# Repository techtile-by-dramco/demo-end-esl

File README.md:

# Energy Neutral Device Demo

In this repository, KU Leuven presents a portable, energy-neutral device demonstrator. The demonstrator showcases the potential of ambient energy harvesting, with a particular emphasis on RF energy harvesting. Its primary objective is to demonstrate the feasibility of a realistic use case, illustrating how low-power devices can operate without conventional power sources. This demonstrator includes an RF-powered Electronic Shelf Label (ESL) that operates entirely without batteries. Instead, the system relies on an aluminium electrolytic capacitor as a short-term energy storage element.

<td></td>

## ToDo
- Add PLL board as RF source

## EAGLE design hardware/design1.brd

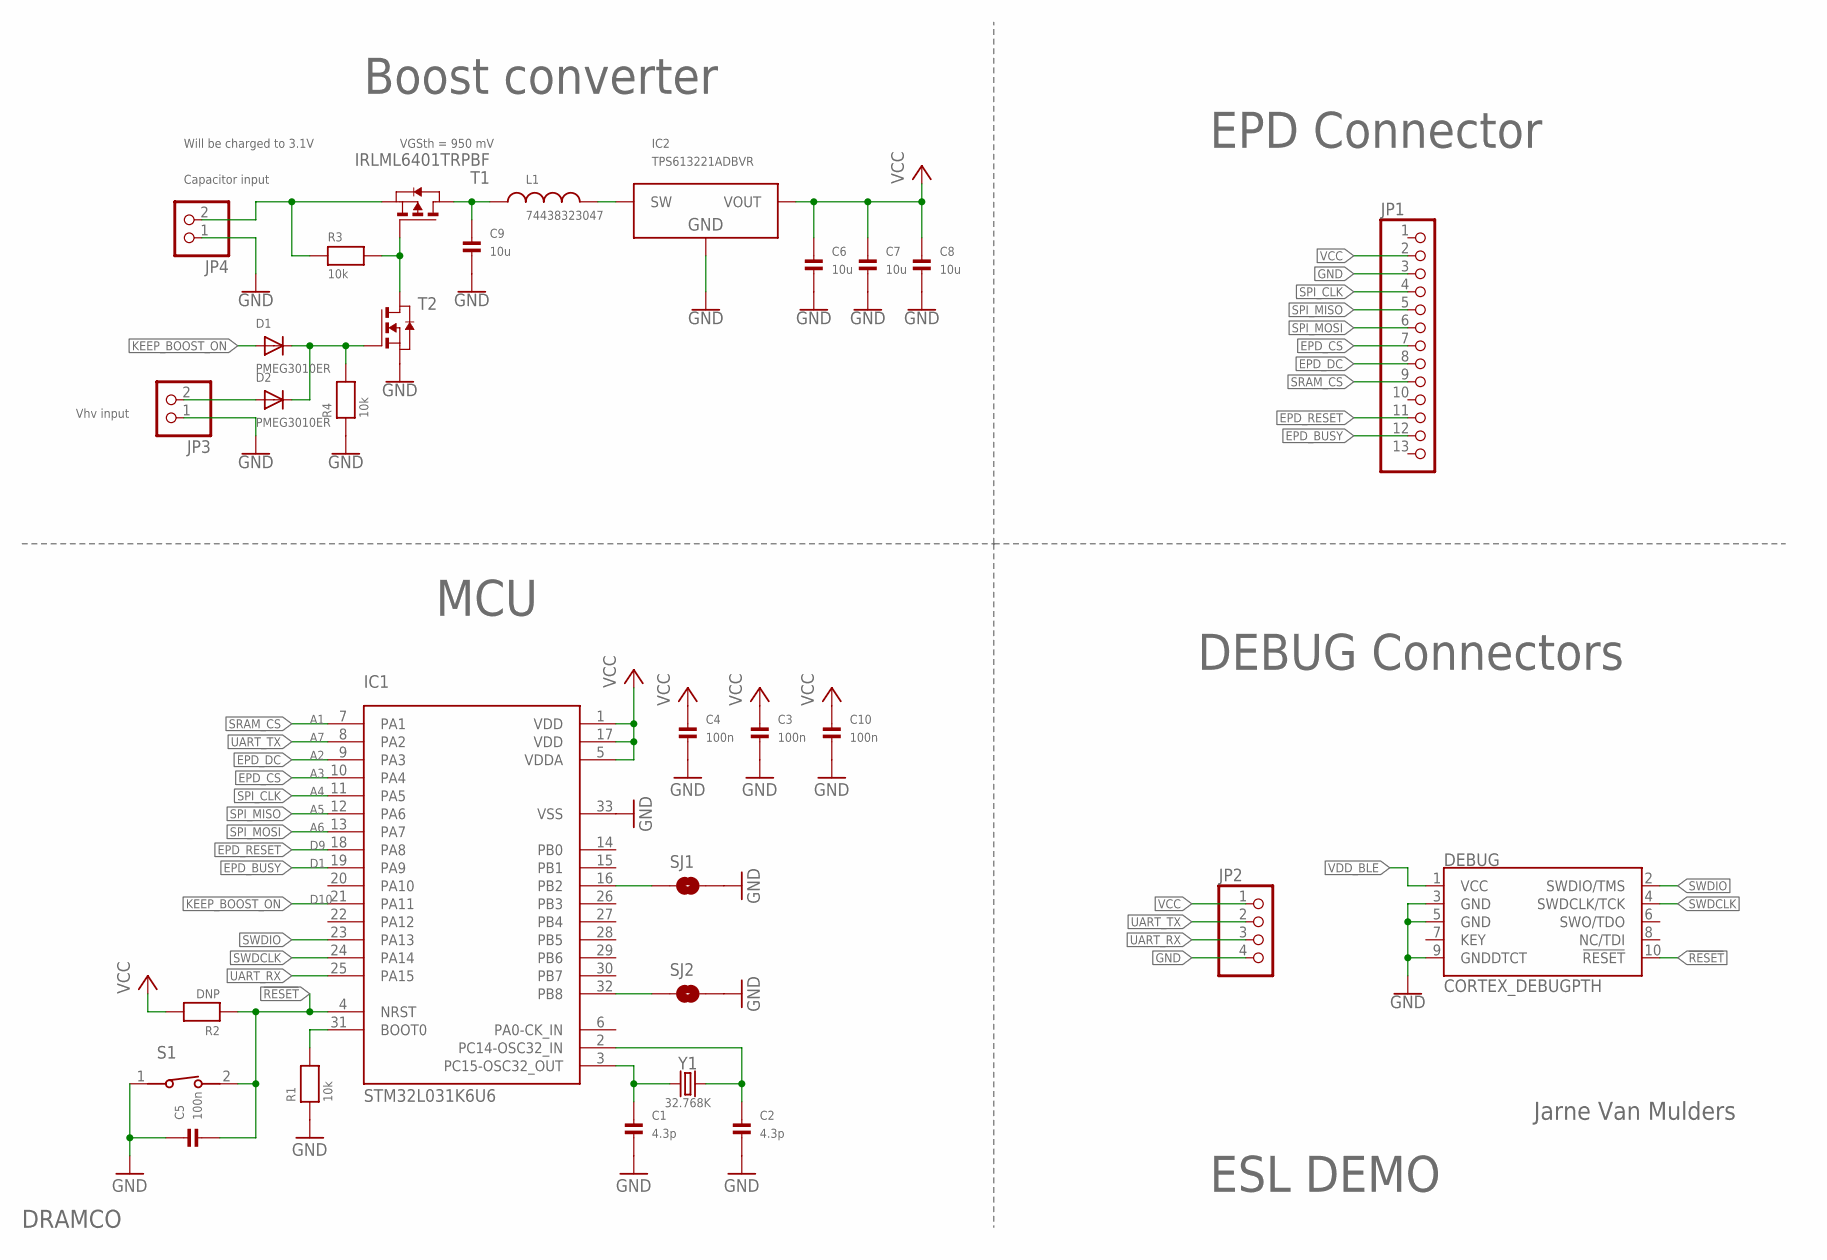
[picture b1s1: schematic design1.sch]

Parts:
C1, C2: 4.3p; 0603
C3, C4, C5, C10: 100n; 0603
C6, C7, C8, C9: 10u; 0805
D1, D2: PMEG3010ER; SOD-323
DEBUG: CORTEX_DEBUGPTH; 2X5-PTH-1.27MM
IC1: STM32L031K6U6; UFQFPN32
IC2: TPS61322XX; SOT95P280X145-5N
JP1: HEADER-1X13; 1X13_ROUND_70
JP2: HEADER-1X4ROUND; 1X04_ROUND
JP3, JP4: HEADER-1X2ROUND; 1X02_ROUND
L1: 74438323047; WE-MAIA_2510
R1, R3, R4: 10k; 0603
R2: DNP; 0603
S1: 434111043826
SJ1, SJ2: SOLDERJUMPERNO; SJ_2S-NO
T1: IRLML6401TRPBF; SOT-23
T2: NMOSSOT23; SOT-23
Y1: 32.768K; CRYSTAL-SMD-3.2X1.5MM

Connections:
!RESET!: C5.2, DEBUG.10 (!RESET), IC1.4 (NRST), R2.1, S1.2
EPD_BUSY: IC1.19 (PA9), JP1.12
EPD_CS: IC1.10 (PA4), JP1.7
EPD_DC: IC1.9 (PA3), JP1.8
EPD_RESET: IC1.18 (PA8), JP1.11
GND: C1.2, C2.2, C3.2, C4.2, C5.1, C6.2, C7.2, C8.2, C9.2, C10.2, DEBUG.3 (GND), DEBUG.5 (GND), DEBUG.9 (GNDDTCT), IC1.33 (VSS), IC2.2 (GND), JP1.3, JP2.4, JP3.1, JP4.1, R1.1, R4.1, S1.1, SJ1.2, SJ2.2, T2.2 (S)
KEEP_BOOST_ON: D1.A, IC1.21 (PA11)
unnamed: IC1.31 (BOOT0), R1.2
unnamed: C2.1, IC1.2 (PC14-OSC32_IN), Y1.P$2 (2)
unnamed: C1.1, IC1.3 (PC15-OSC32_OUT), Y1.P$1 (1)
unnamed: IC1.16 (PB2), SJ1.1
unnamed: IC1.32 (PB8), SJ2.1
unnamed: C9.1, L1.1, T1.1 (D)
unnamed: IC2.1 (SW), L1.2
unnamed: D1.C, D2.C, R4.2, T2.3 (G)
unnamed: R3.2, T1.3 (G), T2.1 (D)
unnamed: JP4.2, R3.1, T1.2 (S)
unnamed: D2.A, JP3.2
SPI_CLK: IC1.11 (PA5), JP1.4
SPI_MISO: IC1.12 (PA6), JP1.5
SPI_MOSI: IC1.13 (PA7), JP1.6
SRAM_CS: IC1.7 (PA1), JP1.9
SWDCLK: DEBUG.4 (SWDCLK/TCK), IC1.24 (PA14)
SWDIO: DEBUG.2 (SWDIO/TMS), IC1.23 (PA13)
UART_RX: IC1.25 (PA15), JP2.3
UART_TX: IC1.8 (PA2), JP2.2
VCC: C3.1, C4.1, C6.1, C7.1, C8.1, C10.1, IC1.1 (VDD), IC1.5 (VDDA), IC1.17 (VDD), IC2.4 (VOUT), JP1.2, JP2.1, R2.2
VDD_BLE: DEBUG.1 (VCC)

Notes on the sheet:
D10
Vhv input
Capacitor input
Will be charged to 3.1V
VGSth = 950 mV
TPS613221ADBVR
Boost converter
MCU
DEBUG Connectors
EPD Connector
Jarne Van Mulders
DRAMCO
ESL DEMO

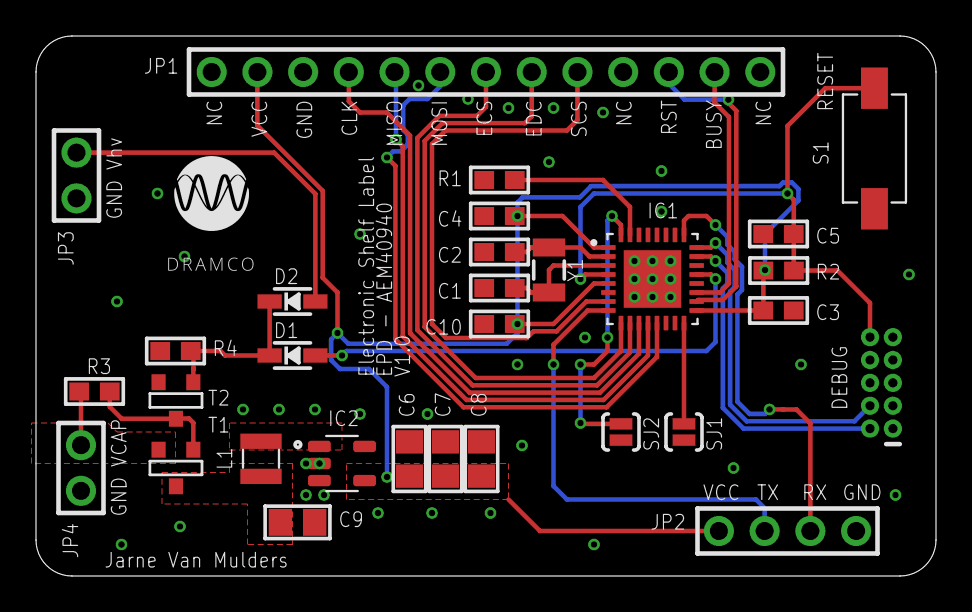
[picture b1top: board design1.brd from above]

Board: 2 copper layers, 50.0 x 30.0 mm, 30 parts (0 on the bottom side), 27 nets.

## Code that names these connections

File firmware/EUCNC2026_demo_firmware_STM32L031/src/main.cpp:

#include <Arduino.h>
#include "Adafruit_ThinkInk.h"
#include <EEPROM.h>

#define EPD_DC        A2//10
#define EPD_CS        A3//9
#define EPD_BUSY      D1//7 // can set to -1 to not use a pin (will wait a fixed delay)
#define SRAM_CS       A1//6
#define EPD_RESET     D9//8  // can set to -1 and share with microcontroller Reset!
#define EPD_SPI       &SPI // primary SPI

#define SPI1_SCK      A4
#define SPI1_MISO     A5
#define SPI1_MOSI     A6

#define KEEP_BOOST_ON D10

//  Frame number (saved in EEPROM)
uint8_t frame_number;
int eeAddress = 0;   // Location we want the data to be put.

//  Static void functions
static void setup_esl(String price);

//  EPD object
ThinkInk_213_Mono_BN display(EPD_DC, EPD_RESET, EPD_CS, SRAM_CS, EPD_BUSY, EPD_SPI);


//  Configure SYSTEM clock - NXP
extern "C" void SystemClock_Config(void){
 RCC_OscInitTypeDef RCC_OscInitStruct = {0};
  RCC_ClkInitTypeDef RCC_ClkInitStruct = {0};
  RCC_PeriphCLKInitTypeDef PeriphClkInit = {0};

  /** Configure the main internal regulator output voltage
  */
  __HAL_PWR_VOLTAGESCALING_CONFIG(PWR_REGULATOR_VOLTAGE_SCALE1);

  /** Initializes the RCC Oscillators according to the specified parameters
  * in the RCC_OscInitTypeDef structure.
  */
  RCC_OscInitStruct.OscillatorType = RCC_OSCILLATORTYPE_LSI|RCC_OSCILLATORTYPE_MSI;
  RCC_OscInitStruct.LSIState = RCC_LSI_ON;
  RCC_OscInitStruct.MSIState = RCC_MSI_ON;
  RCC_OscInitStruct.MSICalibrationValue = 0;
  RCC_OscInitStruct.MSIClockRange = RCC_MSIRANGE_6;
  RCC_OscInitStruct.PLL.PLLState = RCC_PLL_NONE;
  if (HAL_RCC_OscConfig(&RCC_OscInitStruct) != HAL_OK)
  {
    Error_Handler();
  }

  /** Initializes the CPU, AHB and APB buses clocks
  */
  RCC_ClkInitStruct.ClockType = RCC_CLOCKTYPE_HCLK|RCC_CLOCKTYPE_SYSCLK
                              |RCC_CLOCKTYPE_PCLK1|RCC_CLOCKTYPE_PCLK2;
  RCC_ClkInitStruct.SYSCLKSource = RCC_SYSCLKSOURCE_MSI;
  RCC_ClkInitStruct.AHBCLKDivider = RCC_SYSCLK_DIV1;
  RCC_ClkInitStruct.APB1CLKDivider = RCC_HCLK_DIV1;
  RCC_ClkInitStruct.APB2CLKDivider = RCC_HCLK_DIV1;

  if (HAL_RCC_ClockConfig(&RCC_ClkInitStruct, FLASH_LATENCY_0) != HAL_OK)
  {
    Error_Handler();
  }
  PeriphClkInit.PeriphClockSelection = RCC_PERIPHCLK_RTC;
  PeriphClkInit.RTCClockSelection = RCC_RTCCLKSOURCE_LSI;
  if (HAL_RCCEx_PeriphCLKConfig(&PeriphClkInit) != HAL_OK)
  {
    Error_Handler();
  }
}


void setup() {

  Serial.begin(115200);
  while (!Serial) {
    delay(10);
  }

  pinMode(LED_BUILTIN, OUTPUT);   //  Set buildin LED as output
  pinMode(EPD_CS, OUTPUT);        //  Set SS as output

  // SPI config
  SPI.setMOSI(SPI1_MOSI);
  SPI.setMISO(SPI1_MISO);
  SPI.setSCLK(SPI1_SCK);

  //  OVERRULE - Keep BOOST converter ON
  pinMode(KEEP_BOOST_ON, OUTPUT);
  digitalWrite(KEEP_BOOST_ON, HIGH);

  Serial.println("Adafruit EPD full update test in mono");
  display.begin(THINKINK_MONO);
}

void loop() {

  Serial.println("hello");
  
  //  Keep boost on for 3V3 supply voltage during EPD update
  digitalWrite(KEEP_BOOST_ON, HIGH);

  //  Get frame number for EEPROM
  uint8_t new_frame_number;
  frame_number = EEPROM.read(eeAddress);

  //  Decide with update will be performed
  switch (frame_number){
    // ESL layout with price 0.75 dollar
    case 0:
      setup_esl("$0.75");
      new_frame_number = 1;
      break;
    
    // ESL layout with price 1.4 dollar
    case 1:
      setup_esl("$1.40");
      new_frame_number = 2;
      break;
    
    // ESL layout with price 2.5 dollar
    case 2:
      setup_esl("$2.50");
      new_frame_number = 3;
      break;
    
    // Default
    default:
      break;
  }

  //  Store case number in EEPROM
  EEPROM.put(eeAddress, new_frame_number);

  //  Disable 3V3 --> DEADLOCK
  digitalWrite(KEEP_BOOST_ON, LOW);
  delay(500);
}


void setup_esl(String price){
    display.clearBuffer();
    display.setTextSize(1); // Smaller text size for a compact look
    display.setTextColor(EPD_BLACK);

    // Draw a border to mimic an ESL frame
    display.drawRect(0, 0, display.width(), display.height(), EPD_BLACK);

    // Set product information
    display.setCursor(20, 10);
    display.setTextSize(3);
    display.print("PRODUCT NAME");
    display.setCursor(0, 30);
    display.fillRect(10, 38, display.width()-20, 2, EPD_BLACK);
    display.setCursor(140, 68);
    display.setTextSize(3);
    display.print(price);
    display.drawRect(10, 55, display.width()/2-10, display.height()/2-5, EPD_BLACK);
    display.setCursor(28, 75);
    display.setTextSize(2);
    display.print("PICTURE");

    // Display
    display.display();
}

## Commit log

2026-02-16 Add picture
2026-02-16 Enhance README with project description
    Added a description of the energy-neutral device demonstrator and its features.
2026-02-18 Add new measurements
2026-02-18 Update power profile measurements in README
2026-02-18 Update section title and table headers in README
2026-02-18 new measurement
2026-02-18 Update image paths in README for voltage converter
2026-02-18 Comment out image in README
    Commented out the image tag in the README file.
2026-02-20 add pictures
2026-02-20 Add algorithm description and results section to README
    Added a section detailing the dithering algorithm used for display rendering and included results with images.
2026-04-14 Add transmitter firmware
2026-04-14 Update firmware transmitter

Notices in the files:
parts and their libraries:
microbuilder: This work is placed in the public domain, and may be freely used for commercial and non-commercial work with the following conditions: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
SparkFun-Clocks: Licensing: Creative Commons ShareAlike 4.0 International - https://creativecommons.org/licenses/by-sa/4.0
